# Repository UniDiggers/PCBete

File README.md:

# PCBete

Création d'un PCB pour la robotique.

## Objectif :

Carte électronique ESP32-S3-WROOM-U1 permettant de controller : 
- Jusqu'à 3 NEMA 17 
- 3 Capteurs TOF VL53L0X (i2c)
- 1 écran OLED 0.96 128*64 (i2c) 
- Buzzer
- LiDAR*

Alimentation via PowerBank 5Ah avec 5V/3A vers la carte en Type-C vers Type-C .

## Consommation théorique 

**3000mA** sont disponibles :

- 1x ESP32 environ **150mA**
- 3x NEMA 17 environ **2400mA**
- 3x TOF VL53L0X environ **60mA**
- 1x Ecran OLED environ **15mA**
- 1x Buzzer environ **10mA**

**TOTAL THEORIQUE : 2635mA / 87%**
*Ce calcul ne prend pas en compte la consommation théorique des composants soudés à la carte.

*le LiDAR est un accessoire optionnel qui peut être ajouté si la consommation instantanée le permet.
1x LiDAR environ **150mA**.

TOTAL THEORIQUE avec LiDAR : **2785mA / 92%**

## Temps d'utilisation théorique

Energie Batterie = Capacité (Ah) x Tension sortie ( Volt).
Energie Batterie = 5Ah x 5 = **25Wh**.

Puissance carte = Intensité (A) x Tension (Volt).
Puissance carte = 3A x 5V = **15W**.

Temps d'utilisation (heure) = Energie Batterie (watt-heures) / Puissance carte (W).
Temps d'utilisation (heure) = 25Wh / 15W = **1.67 heures**.

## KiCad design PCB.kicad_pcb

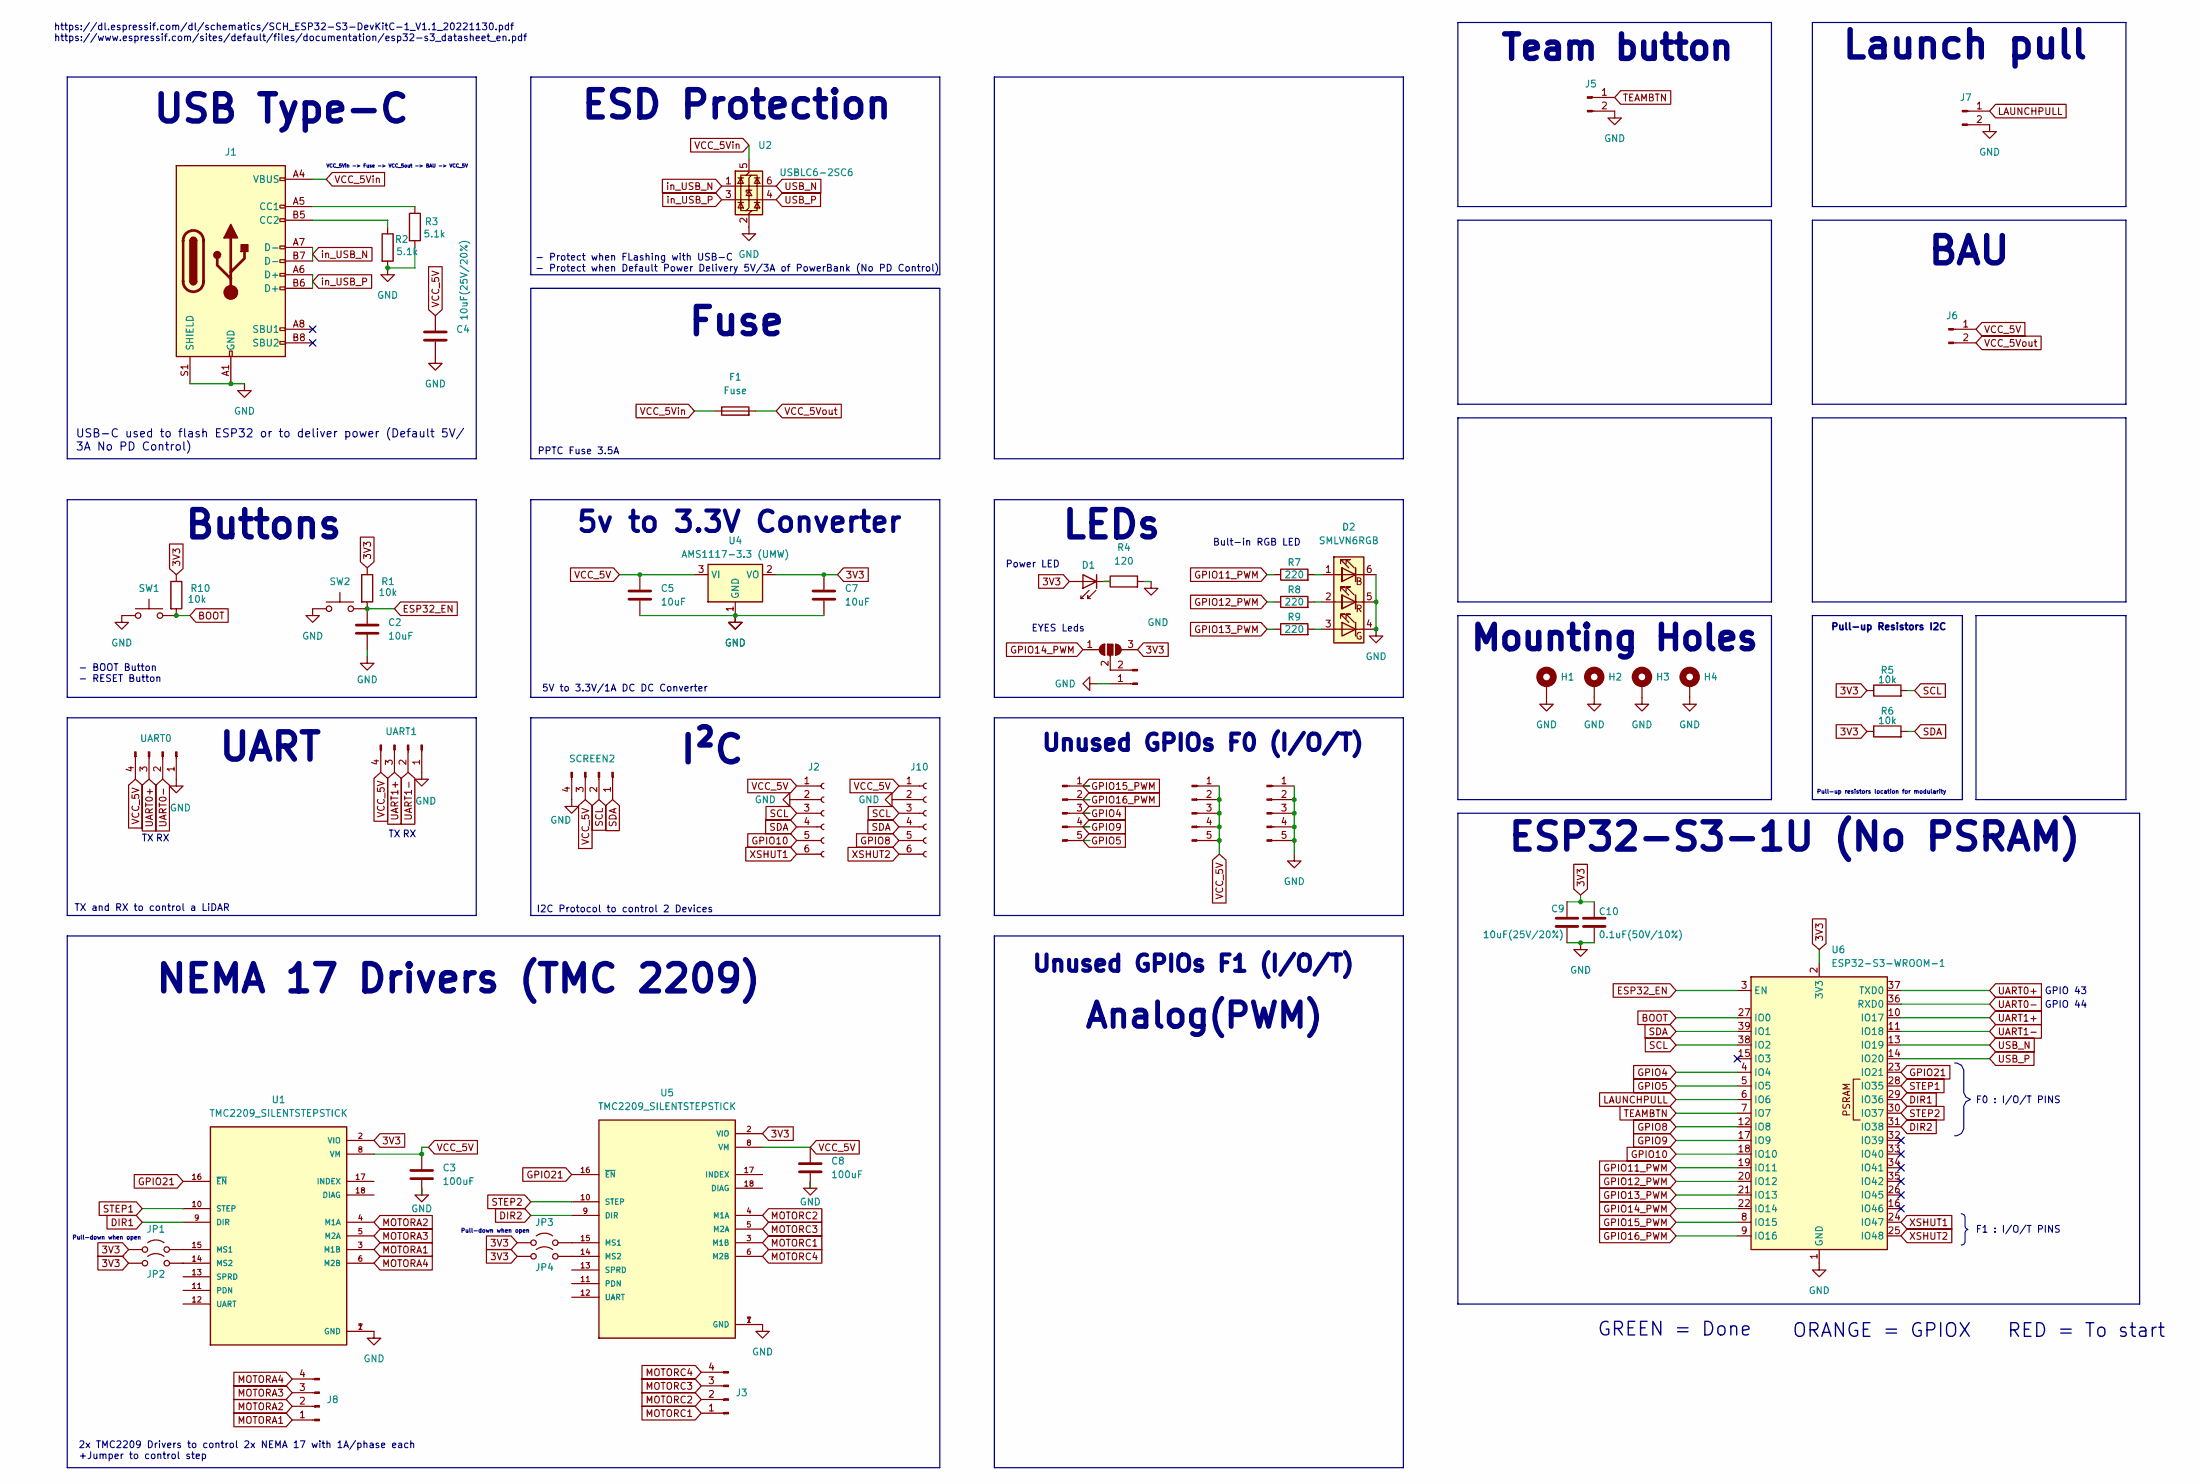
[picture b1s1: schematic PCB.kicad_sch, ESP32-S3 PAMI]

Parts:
C2: 10uF; C_0805_2012Metric_Pad1.18x1.45mm_HandSolder
C3, C8: 100uF; CP_Elec_4x5.7
C4: 10uF(25V/20%); R_0805_2012Metric_Pad1.20x1.40mm_HandSolder
C5, C7: 10uF; C_1206_3216Metric_Pad1.33x1.80mm_HandSolder
C9: 10uF(25V/20%); C_0805_2012Metric_Pad1.18x1.45mm_HandSolder
C10: 0.1uF(50V/10%); C_0805_2012Metric_Pad1.18x1.45mm_HandSolder
D1: LED_0805_2012Metric_Pad1.15x1.40mm_HandSolder
D2: SMLVN6RGB; LED_RGB_5050-6
F1: Fuse; Fuse_1206_3216Metric
H1, H2, H3, H4: MountingHole_Pad; MountingHole_3.2mm_M3_Pad
J1: USB_C_Receptacle_USB2.0_16P; USB_C_Receptacle_HRO_TYPE-C-31-M-12
J2, J10: Conn_01x06_Socket; PinSocket_1x06_P2.54mm_Vertical
J3, J8: Conn_01x04_Pin; PinHeader_1x04_P2.54mm_Vertical
J4, J9, J13: Conn_01x05_Pin; PinHeader_1x05_P2.54mm_Vertical
J5, J6, J7, J11: Conn_01x02_Pin; PinHeader_1x02_P2.54mm_Vertical
JP1, JP2, JP3, JP4: Jumper_2_Open; PinHeader_1x02_P2.54mm_Vertical
JP5: SolderJumper_3_Open; SolderJumper-3_P1.3mm_Open_Pad1.0x1.5mm
R1, R5, R6, R10: 10k; R_1206_3216Metric_Pad1.30x1.75mm_HandSolder
R2, R3: 5.1k; R_0805_2012Metric_Pad1.20x1.40mm_HandSolder
R4: 120; R_0805_2012Metric_Pad1.20x1.40mm_HandSolder
R7, R8, R9: 220; R_0805_2012Metric_Pad1.20x1.40mm_HandSolder
SCREEN2: Conn_01x04_Pin; PinSocket_1x04_P2.54mm_Vertical
SW1, SW2: SW_Push; SW_Push_SPST_NO_Alps_SKRK
U1, U5: TMC2209_SILENTSTEPSTICK; MODULE_TMC2209_SILENTSTEPSTICK; PARTREV 1.20
U2: USBLC6-2SC6; SOT-23-6_Handsoldering
U4: AMS1117-3.3 (UMW); SOT-223-3_TabPin2
U6: ESP32-S3-WROOM-1; ESP32-S3-WROOM-1U
UART0, UART1: Conn_01x04_Pin; PinHeader_1x04_P2.54mm_Vertical

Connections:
3V3: C7.1, C9.1, C10.1, D1.2 (A), JP1.1 (A), JP2.1 (A), JP3.1 (A), JP4.1 (A), JP5.3 (B), R1.1, R5.1, R6.1, R10.1, U1.2 (VIO), U4.2 (VO), U5.2 (VIO), U6.2 (3V3)
BOOT: R10.2, SW1.2, U6.27 (IO0)
DIR1: U1.9 (DIR), U6.29 (IO36)
DIR2: U5.9 (DIR), U6.31 (IO38)
ESP32_EN: C2.1, R1.2, SW2.2, U6.3 (EN)
GND: C2.2, C3.2, C4.2, C5.2, C7.2, C8.2, C9.2, C10.2, D2.4 (GK), D2.5 (RK), D2.6 (BK), H1.1, H2.1, H3.1, H4.1, J1.A1 (GND), J1.A12 (GND), J1.B1 (GND), J1.B12 (GND), J1.S1 (SHIELD), J2.2, J5.2, J7.2, J10.2, J11.1, J13.1, J13.2, J13.3, J13.4, J13.5, R2.2, R3.2, R4.2, SCREEN2.4, SW1.1, SW2.1, U1.1 (GND), U1.7 (GND), U2.2 (GND), U4.1 (GND), U5.1 (GND), U5.7 (GND), U6.1 (GND), U6.40 (GND), U6.41 (GND), UART0.1, UART1.1
GPIO4: J4.3, U6.4 (IO4)
GPIO5: J4.5, U6.5 (IO5)
GPIO8: J10.5, U6.12 (IO8)
GPIO9: J4.4, U6.17 (IO9)
GPIO10: J2.5, U6.18 (IO10)
GPIO11_PWM: R7.1, U6.19 (IO11)
GPIO12_PWM: R8.1, U6.20 (IO12)
GPIO13_PWM: R9.1, U6.21 (IO13)
GPIO14_PWM: JP5.1 (A), U6.22 (IO14)
GPIO15_PWM: J4.1, U6.8 (IO15)
GPIO16_PWM: J4.2, U6.9 (IO16)
GPIO21: U1.16 (~EN), U5.16 (~EN), U6.23 (IO21)
LAUNCHPULL: J7.1, U6.6 (IO6)
MOTORA1: J8.1, U1.3 (M1B)
MOTORA2: J8.2, U1.4 (M1A)
MOTORA3: J8.3, U1.5 (M2A)
MOTORA4: J8.4, U1.6 (M2B)
MOTORC1: J3.1, U5.3 (M1B)
MOTORC2: J3.2, U5.4 (M1A)
MOTORC3: J3.3, U5.5 (M2A)
MOTORC4: J3.4, U5.6 (M2B)
unnamed: D1.1 (K), R4.1
unnamed: D2.1 (BA), R7.2
unnamed: D2.3 (GA), R9.2
unnamed: D2.2 (RA), R8.2
unnamed: J1.A5 (CC1), R3.1
unnamed: J1.B5 (CC2), R2.1
unnamed: J11.2, JP5.2 (C)
unnamed: JP1.2 (B), U1.15 (MS1)
unnamed: JP2.2 (B), U1.14 (MS2)
unnamed: JP3.2 (B), U5.15 (MS1)
unnamed: JP4.2 (B), U5.14 (MS2)
SCL: J2.3, J10.3, R5.2, SCREEN2.2, U6.38 (IO2)
SDA: J2.4, J10.4, R6.2, SCREEN2.1, U6.39 (IO1)
STEP1: U1.10 (STEP), U6.28 (IO35)
STEP2: U5.10 (STEP), U6.30 (IO37)
TEAMBTN: J5.1, U6.7 (IO7)
UART0+: U6.37 (TXD0), UART0.3
UART0-: U6.36 (RXD0), UART0.2
UART1+: U6.10 (IO17), UART1.3
UART1-: U6.11 (IO18), UART1.2
USB_N: U2.6 (I/O1), U6.13 (IO19)
USB_P: U2.4 (I/O2), U6.14 (IO20)
VCC_5V: C3.1, C4.1, C5.1, C8.1, J2.1, J6.1, J9.1, J9.2, J9.3, J9.4, J9.5, J10.1, SCREEN2.3, U1.8 (VM), U4.3 (VI), U5.8 (VM), UART0.4, UART1.4
VCC_5Vin: F1.1, J1.A4 (VBUS), J1.A9 (VBUS), J1.B4 (VBUS), J1.B9 (VBUS), U2.5 (VBUS)
VCC_5Vout: F1.2, J6.2
XSHUT1: J2.6, U6.24 (IO47)
XSHUT2: J10.6, U6.25 (IO48)
in_USB_N: J1.A7 (D-), J1.B7 (D-), U2.1 (I/O1)
in_USB_P: J1.A6 (D+), J1.B6 (D+), U2.3 (I/O2)

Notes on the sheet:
USB-C used to flash ESP32 or to deliver power (Default 5V/ 3A No PD Control)
Pull-up Resistors I2C
I²C
2x TMC2209 Drivers to control 2x NEMA 17 with 1A/phase each +Jumper to control step
Bult-in RGB LED
PPTC Fuse 3.5A
Pull-down when open
Unused GPIOs F1 (I/O/T)
EYES Leds
Buttons
GREEN = Done
ESP32-S3-1U (No PSRAM)
RED = To start
BAU
USB Type-C
5v to 3.3V Converter
5V to 3.3V/1A DC DC Converter
https://www.espressif.com/sites/default/files/documentation/esp32-s3_datasheet_en.pdf
F0 : I/O/T PINS
Unused GPIOs F0 (I/O/T)
Power LED
GPIO 44
ESD Protection
Mounting Holes
TX and RX to control a LiDAR
Pull-up resistors location for modularity
GPIO 43
VCC_5Vin -> Fuse -> VCC_5out -> BAU -> VCC_5V
Team button
ORANGE = GPIOX
Fuse
Analog(PWM)
NEMA 17 Drivers (TMC 2209)
UART
Pull-down when open
https://dl.espressif.com/dl/schematics/SCH_ESP32-S3-DevKitC-1_V1.1_20221130.pdf
I2C Protocol to control 2 Devices
Launch pull
- BOOT Button - RESET Button
LEDs

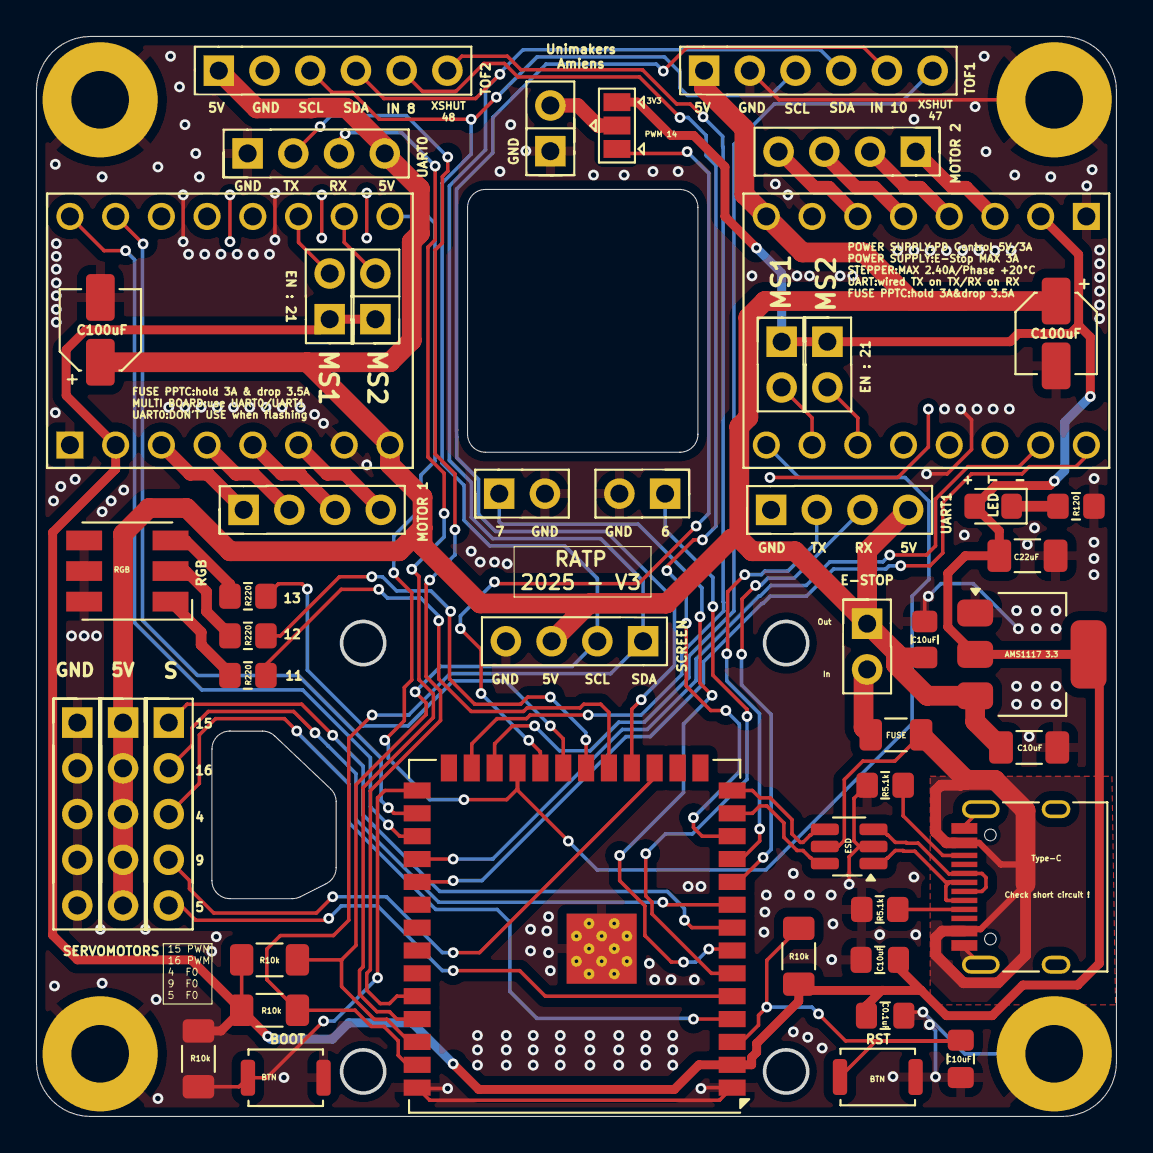
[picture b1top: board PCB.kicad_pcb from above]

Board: 2 copper layers, 60.0 x 60.0 mm, 52 parts (0 on the bottom side), 56 nets.

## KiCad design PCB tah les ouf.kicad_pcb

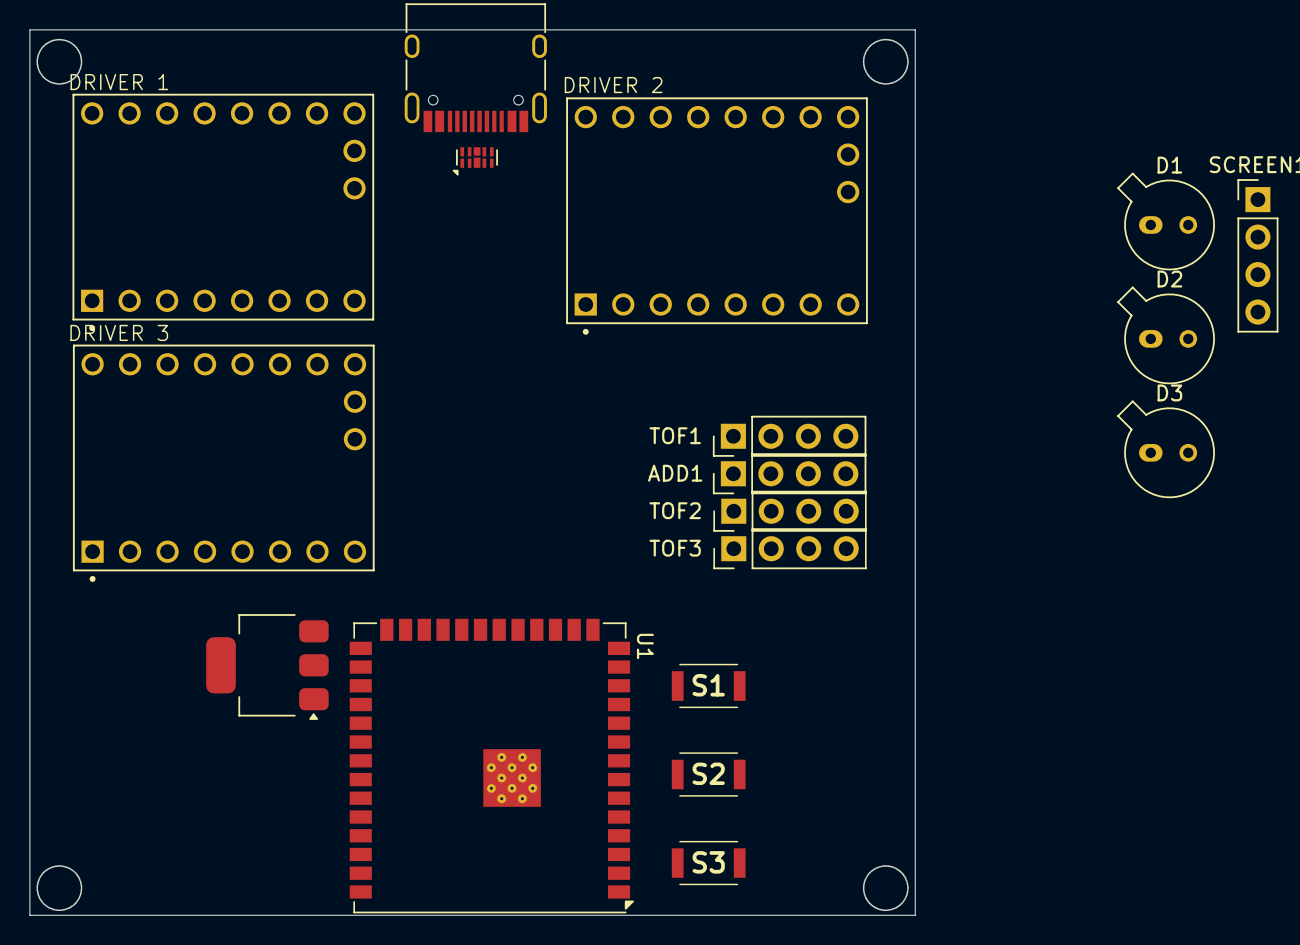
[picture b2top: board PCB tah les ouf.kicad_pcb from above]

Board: 2 copper layers, 60.0 x 60.0 mm, 18 parts (0 on the bottom side), 9 nets, no tracks yet.

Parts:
ADD1: Conn_01x04_Pin; PinHeader_1x04_P2.54mm_Vertical
D1, D2, D3: TO-18-2_Window
J1: USB_C_Receptacle_USB2.0_16P; USB_C_Receptacle_HRO_TYPE-C-31-M-12
S1: BOOT; SKRKAEE020
S2: RST; SKRKAEE020
S3: BUILTIN; SKRKAEE020
SCREEN1: Conn_01x04_Pin; PinHeader_1x04_P2.54mm_Vertical
TOF1, TOF2, TOF3: Conn_01x04_Pin; PinHeader_1x04_P2.54mm_Vertical
U1: ESP32-S3-WROOM-1; ESP32-S3-WROOM-1U
U2, U3, U4: TMC2209_SILENTSTEPSTICK; MODULE_TMC2209_SILENTSTEPSTICK
U6: D3V3XA4B10LP; Diodes_UDFN-10_1.0x2.5mm_P0.5mm
U7: AMS1117-3.3 (UMW); SOT-223-3_TabPin2

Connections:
/3V3: U1.2 (3V3), U7.2 (VO)
/ESP32_EN: S2.2, U1.3 (EN)
/GPIO0: S1.2, U1.27 (IO0)
/USB_N: J1.A7 (D-), J1.B7 (D-), U1.13 (IO19), U6.1, U6.10 (NC)
/USB_P: J1.A6 (D+), J1.B6 (D+), U1.14 (IO20), U6.2, U6.9 (NC)
GND: ADD1.4, J1.A1 (GND), J1.A12 (GND), J1.B1 (GND), J1.B12 (GND), J1.S1 (SHIELD), S1.1, S2.1, S3.1, SCREEN1.4, TOF1.4, TOF2.4, TOF3.4, U1.1 (GND), U1.40 (GND), U1.41 (GND), U2.1 (GND), U2.7 (GND), U3.1 (GND), U3.7 (GND), U4.1 (GND), U4.7 (GND), U6.3 (VSS), U6.8 (VSS), U7.1 (GND)
SCL: ADD1.2, SCREEN1.2, TOF1.2, TOF2.2, TOF3.2, U1.11 (IO18)
SDA: ADD1.1, SCREEN1.1, TOF1.1, TOF2.1, TOF3.1, U1.10 (IO17)
VCC_5V: ADD1.3, D1.2 (A), D2.2 (A), D3.2 (A), J1.A4 (VBUS), J1.A9 (VBUS), J1.B4 (VBUS), J1.B9 (VBUS), SCREEN1.3, TOF1.3, TOF2.3, TOF3.3, U6.4, U6.7 (NC), U7.3 (VI)

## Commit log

2024-06-10 init commit
2024-06-10 Ajout variables de chemin
2024-06-10 Ajout ESP32-S3-WROOM-1U
2024-06-10 Ajustement TMC
2024-06-10 AJOUT driver stepper
2024-06-11 Fix problem / ESD Protection
2024-06-11 correction problemes
2024-06-11 Ajout Auto flash mode
2024-06-11 auto flash mode v2
2024-06-14 Ajout switches DIP drivers & 5 to 3.3 converter
2024-06-14 Fix 5 to 3.3 converter
2024-06-14 ajout boutons rst,boot,builtin
2024-06-14 Add buttons for reset, boot, and built-in functions
2024-07-08 Suppression TMC2209 x1
2024-07-10 Correction label + terminé i2c/uart
2024-07-13 Ajout MD et correction erreurs
2024-07-13 correction erreur clacul
2024-09-13 Ajout empreintes
2024-09-13 Fix court-circuit
2024-09-13 Correction bug schématic
2024-09-14 routage terminé
2024-09-15 chnagement jumper + orga
2024-09-15 ajout plus de 5V et GND
2024-09-16 Test DRC + corrections
2024-09-16 ajout hub 3.3v
2024-09-16 Dernier DRC après modicifications
2024-09-17 ajout plan de masse
2024-09-17 ajout trous de montage
2024-09-17 BOM à réaliser
2024-09-19 Test DRC OK
2025-02-02 V2 avec test DRC OK
2025-03-21 debut V3
2025-03-24 fin du routage
2025-03-26 serigraphie
2025-04-20 ajout largeur piste + fix erreurs (DRC NOK)
2025-04-28 fin routage + faire Trou Screen gnd
2025-04-29 test DRC V3 OK prod
2025-09-12 V3 Corrigée (ToF)
2025-09-24 fix condo + sériegraphie
2025-09-24 2ème fix condo boot
2026-02-09 suppression C boot + ajout R boot
